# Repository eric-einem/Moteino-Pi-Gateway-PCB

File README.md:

# Moteino-Pi-Gateway-PCB
PCB for connecting a Moteino to a Raspbery Pi B+

Connects a Moteino to the Raspberry Pi B+ using the Serial Port.

It is designed to fit in a flirc case.

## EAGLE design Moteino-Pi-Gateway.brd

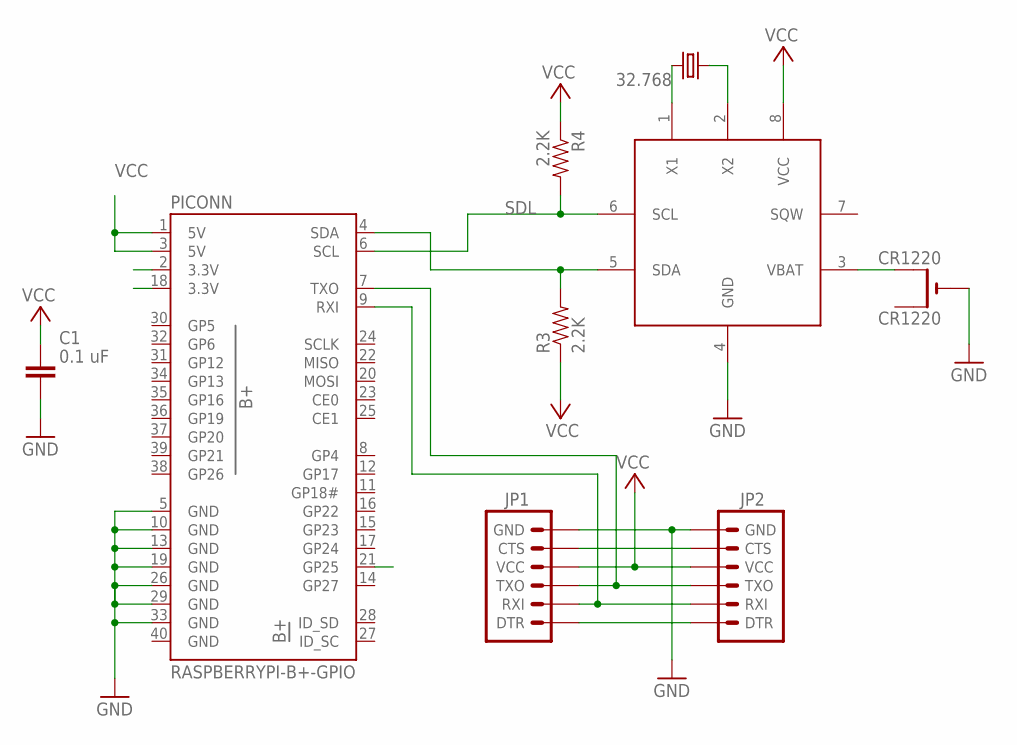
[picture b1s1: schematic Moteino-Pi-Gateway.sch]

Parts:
32.768: CRYTALTC38H; TC38H
1307: DS1307; SO8
C1: 0.1 uF; C1206
CR1220: CR1220; CR1220-THM
JP1, JP2: ARDUINO_SERIAL_PROGRAMLOCK; 1X06_LOCK
PICONN: RASPBERRYPI-B+-GPIO; 2X20-SHROUDED
R3, R4: 2.2K; 0805

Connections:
3.3V: PICONN.2 (3.3V)
3.3V2: PICONN.18 (3.3V)
GND: 1307.4 (GND), C1.2, CR1220.-, JP1.6 (GND), JP2.6 (GND), PICONN.5 (GND), PICONN.10 (GND), PICONN.13 (GND), PICONN.19 (GND), PICONN.26 (GND), PICONN.29 (GND), PICONN.33 (GND), PICONN.40 (GND)
unnamed: 1307.3 (VBAT), CR1220.+2 (+1)
unnamed: 32.768.2, 1307.1 (X1)
unnamed: 32.768.1, 1307.2 (X2)
unnamed: JP1.2 (RXI), JP2.2 (RXI), PICONN.9 (RXI)
unnamed: JP1.3 (TXO), JP2.3 (TXO), PICONN.7 (TXO)
unnamed: JP1.5 (CTS), JP2.5 (CTS)
unnamed: JP1.1 (DTR), JP2.1 (DTR)
SDA: 1307.5 (SDA), PICONN.4 (SDA), R3.2
SDL: 1307.6 (SCL), PICONN.6 (SCL), R4.2
VCC: 1307.8 (VCC), C1.1, JP1.4 (VCC), JP2.4 (VCC), PICONN.1 (5V), PICONN.3 (5V), R3.1, R4.1

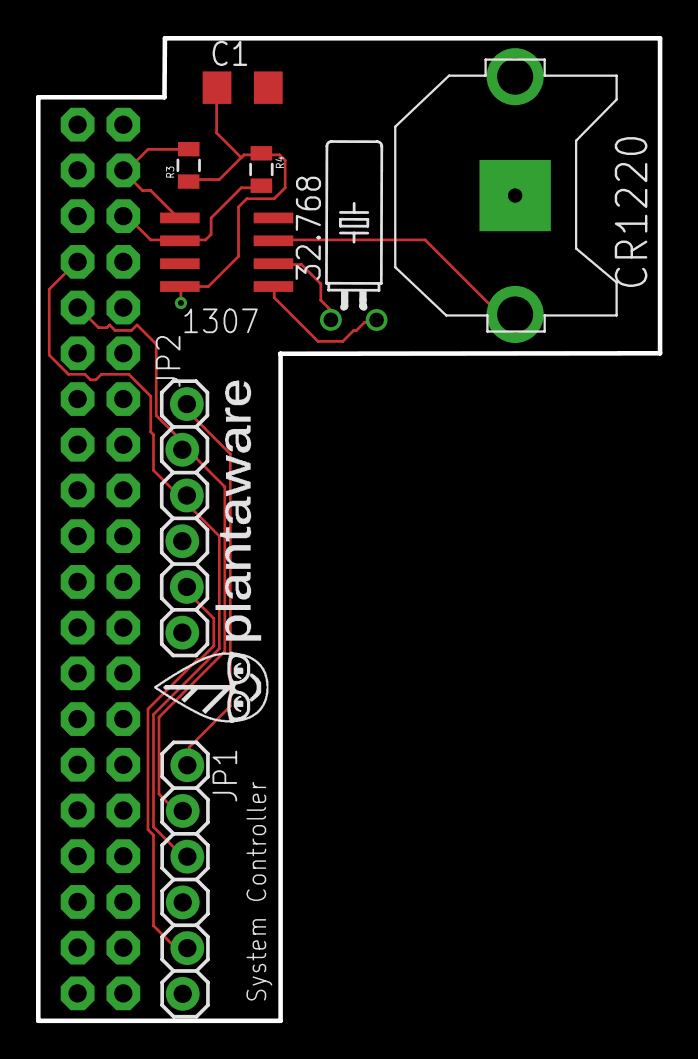
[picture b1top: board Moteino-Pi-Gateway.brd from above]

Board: 2 copper layers, 34.5 x 54.6 mm, 10 parts (1 on the bottom side), 11 nets.

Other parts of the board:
U$1: LOGO_08_INCH

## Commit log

2015-05-06 PCB for Moteino-Pi Gateway. Includes battery-backed up clock as well.

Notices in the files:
parts and their libraries:
SparkFun-Boards: Licensing: Creative Commons ShareAlike 4.0 International - https://creativecommons.org/licenses/by-sa/4.0
